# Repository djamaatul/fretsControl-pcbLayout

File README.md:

# fretsControl-pcbLayout

Sketch : [FretsControl.ino](https://github.com/djamaatul/FretsControl.ino)

## make with Kicad

### project maked :

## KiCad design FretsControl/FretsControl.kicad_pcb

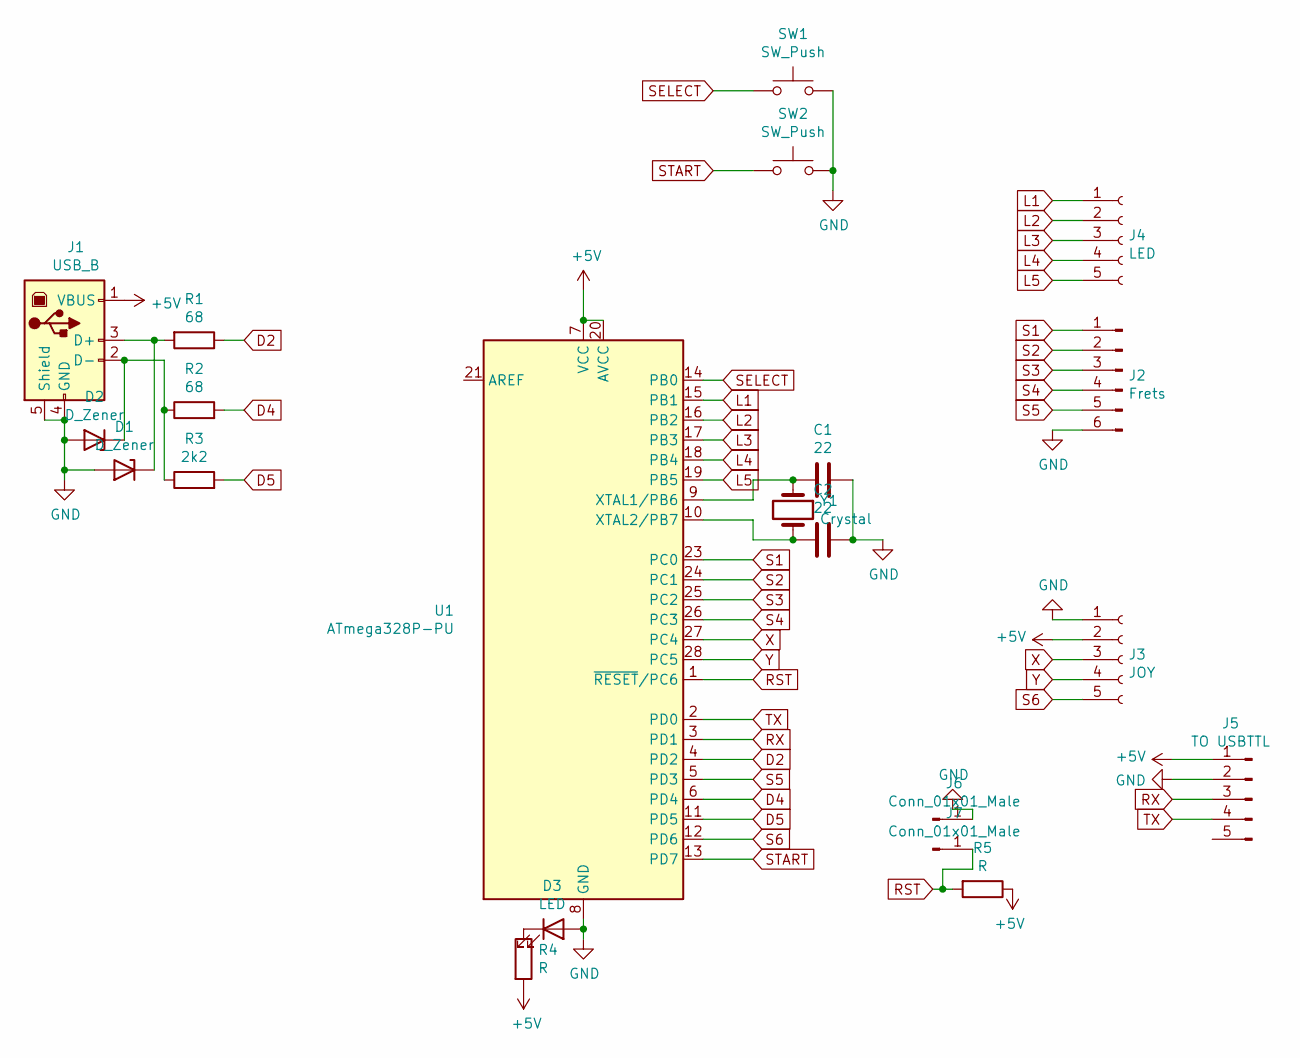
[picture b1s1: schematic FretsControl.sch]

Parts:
C1, C2: 22; C_Disc_D3.0mm_W1.6mm_P2.50mm
D1, D2: D_Zener; D_A-405_P7.62mm_Horizontal
D3: LED; LED_D5.0mm
J1: USB_B; USB_B_OST_USB-B1HSxx_Horizontal
J2: Frets; JST_EH_B6B-EH-A_1x06_P2.50mm_Vertical
J3: JOY; PinSocket_1x05_P2.54mm_Vertical
J4: LED; JST_EH_B5B-EH-A_1x05_P2.50mm_Vertical
J5: TO USBTTL; PinSocket_1x05_P2.54mm_Vertical
J6, J7: Conn_01x01_Male; PinSocket_1x01_P2.54mm_Vertical
R1, R2: 68; R_Axial_DIN0207_L6.3mm_D2.5mm_P10.16mm_Horizontal
R3: 2k2; R_Axial_DIN0207_L6.3mm_D2.5mm_P10.16mm_Horizontal
R4, R5: R; R_Axial_DIN0207_L6.3mm_D2.5mm_P10.16mm_Horizontal
SW1, SW2: SW_Push; SW_Cherry_MX_1.00u_PCB
U1: ATmega328P-PU; DIP-28_W7.62mm
Y1: Crystal; Crystal_HC49-4H_Vertical

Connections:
+5V: J1.1 (VBUS), J3.2, J5.1, R4.2, R5.1, U1.7 (VCC), U1.20 (AVCC)
D2: R1.1, U1.4 (PD2)
D4: R2.2, U1.6 (PD4)
D5: R3.2, U1.11 (PD5)
GND: C1.1, C2.1, D1.2 (A), D2.2 (A), D3.2 (A), J1.4 (GND), J1.5 (Shield), J2.6, J3.1, J5.2, J6.1, SW1.2, SW2.2, U1.8 (GND), U1.22 (GND)
L1: J4.1, U1.15 (PB1)
L2: J4.2, U1.16 (PB2)
L3: J4.3, U1.17 (PB3)
L4: J4.4, U1.18 (PB4)
L5: J4.5, U1.19 (PB5)
unnamed: C1.2, U1.9 (XTAL1/PB6), Y1.1
unnamed: C2.2, U1.10 (XTAL2/PB7), Y1.2
unnamed: D1.1 (K), J1.3 (D+), R1.2
unnamed: D2.1 (K), J1.2 (D-), R2.1, R3.1
unnamed: D3.1 (K), R4.1
RST: J7.1, R5.2, U1.1 (~RESET~/PC6)
RX: J5.3, U1.3 (PD1)
S1: J2.1, U1.23 (PC0)
S2: J2.2, U1.24 (PC1)
S3: J2.3, U1.25 (PC2)
S4: J2.4, U1.26 (PC3)
S5: J2.5, U1.5 (PD3)
S6: J3.5, U1.12 (PD6)
SELECT: SW1.1, U1.14 (PB0)
START: SW2.1, U1.13 (PD7)
TX: J5.4, U1.2 (PD0)
X: J3.3, U1.27 (PC4)
Y: J3.4, U1.28 (PC5)

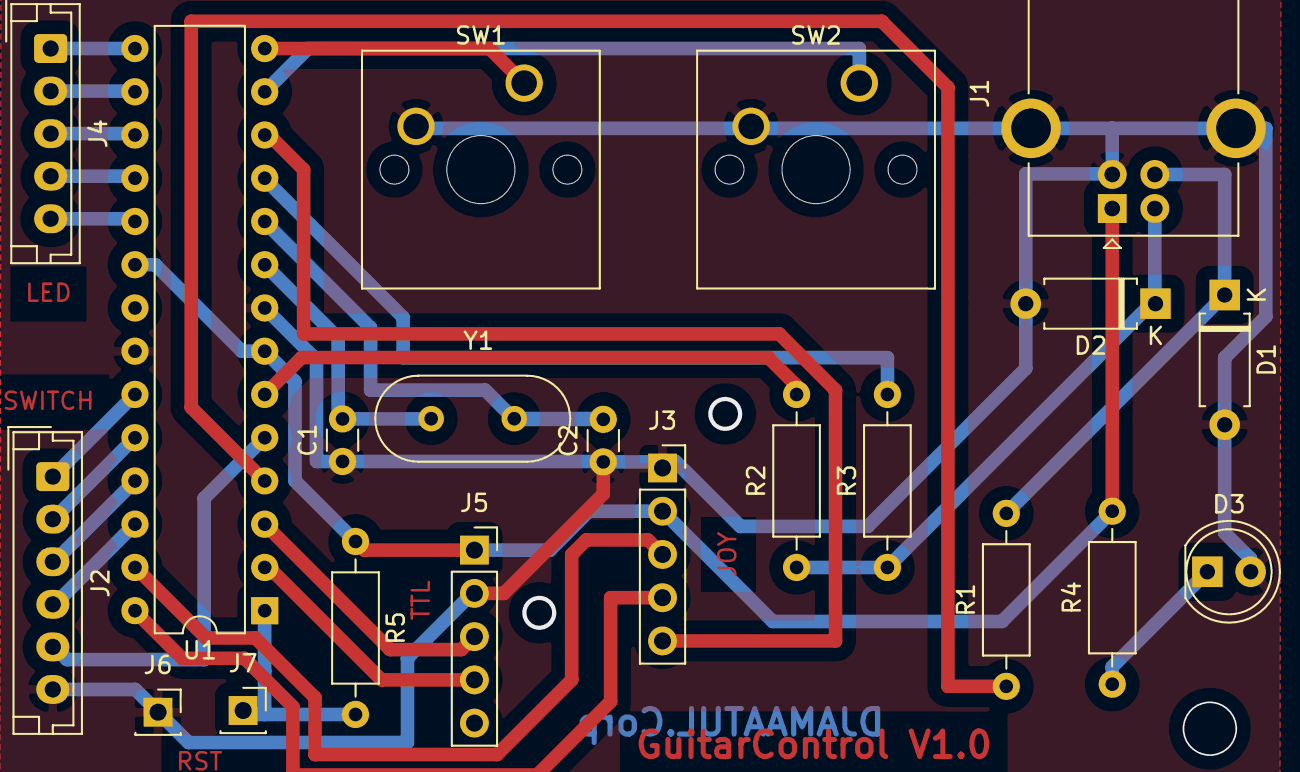
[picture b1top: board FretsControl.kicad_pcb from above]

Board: 2 copper layers, 21 parts (0 on the bottom side), 28 nets.

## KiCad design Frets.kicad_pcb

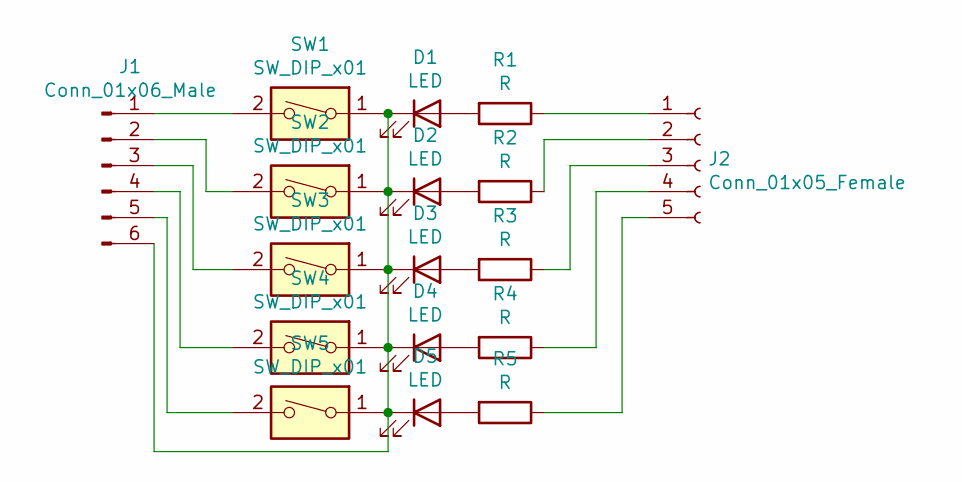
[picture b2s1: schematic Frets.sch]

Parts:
D1, D2, D3, D4, D5: LED; LED_D5.0mm
J1: Conn_01x06_Male; JST_EH_B6B-EH-A_1x06_P2.50mm_Vertical
J2: Conn_01x05_Female; JST_EH_B5B-EH-A_1x05_P2.50mm_Vertical
R1, R2, R3, R4, R5: R; R_Axial_DIN0207_L6.3mm_D2.5mm_P10.16mm_Horizontal
SW1, SW2, SW3, SW4, SW5: SW_DIP_x01; SW_Cherry_MX_1.00u_PCB

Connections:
unnamed: D1.1 (K), D2.1 (K), D3.1 (K), D4.1 (K), D5.1 (K), J1.6, SW1.1, SW2.1, SW3.1, SW4.1, SW5.1
unnamed: D1.2 (A), R1.2
unnamed: D2.2 (A), R2.2
unnamed: D3.2 (A), R3.2
unnamed: D4.2 (A), R4.2
unnamed: D5.2 (A), R5.2
unnamed: J1.1, SW1.2
unnamed: J1.2, SW2.2
unnamed: J1.3, SW3.2
unnamed: J1.4, SW4.2
unnamed: J1.5, SW5.2
unnamed: J2.1, R1.1
unnamed: J2.2, R2.1
unnamed: J2.3, R3.1
unnamed: J2.4, R4.1
unnamed: J2.5, R5.1

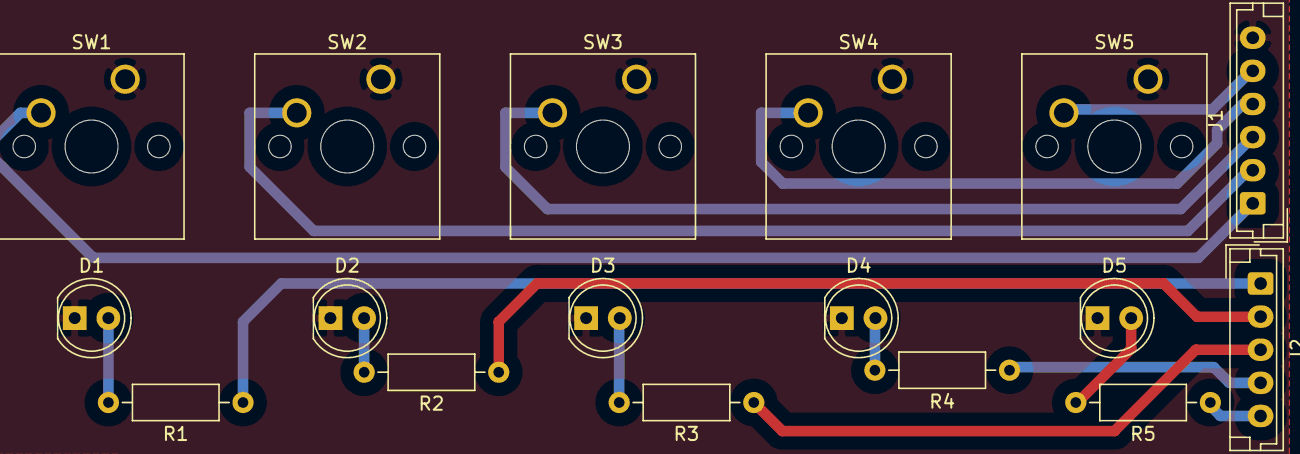
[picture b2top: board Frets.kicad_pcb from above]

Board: 2 copper layers, 17 parts (0 on the bottom side), 16 nets.

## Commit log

2021-11-30 frist commit
2021-11-30 image render of pcb layout
2021-11-30 make markdown
2021-11-30 update link
